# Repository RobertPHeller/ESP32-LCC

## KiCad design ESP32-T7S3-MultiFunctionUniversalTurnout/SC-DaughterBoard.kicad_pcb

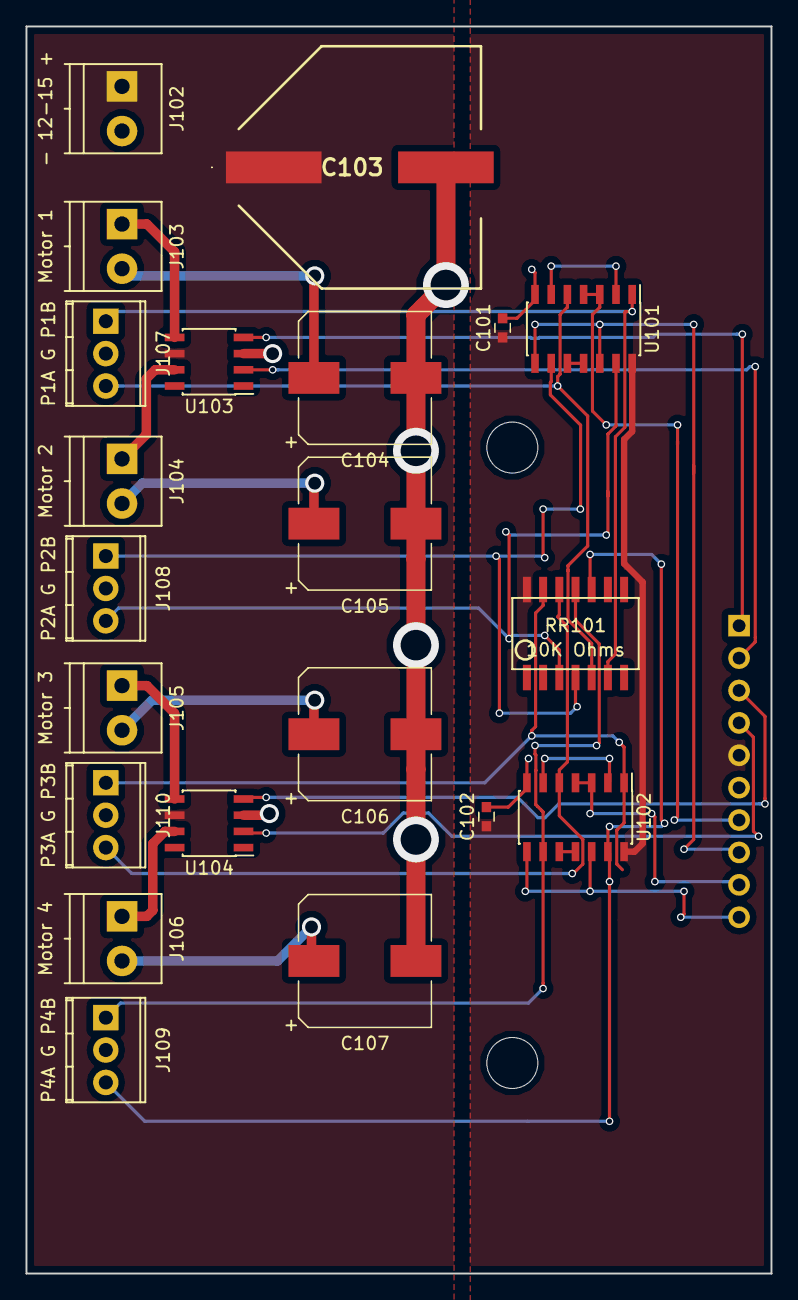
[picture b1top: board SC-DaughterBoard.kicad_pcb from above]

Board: 2 copper layers, 58.4 x 97.8 mm, 22 parts (1 on the bottom side), 31 nets.

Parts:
C101, C102: .1 uf; C_0603
C103: 4700uf 25V; EEEFK0J133SM
C104, C105, C106, C107: 1000uf 25V; CP_Elec_10x10.5
J101: IO_Port; Pin_Header_Straight_1x10_Pitch2.54mm
J102: - 12-15 +; TerminalBlock_Pheonix_PT-3.5mm_2pol
J103: Motor 1; TerminalBlock_Pheonix_PT-3.5mm_2pol
J104: Motor 2; TerminalBlock_Pheonix_PT-3.5mm_2pol
J105: Motor 3; TerminalBlock_Pheonix_PT-3.5mm_2pol
J106: Motor 4; TerminalBlock_Pheonix_PT-3.5mm_2pol
J107: P1A G P1B; TerminalBlock_Pheonix_MPT-2.54mm_3pol
J108: P2A G P2B; TerminalBlock_Pheonix_MPT-2.54mm_3pol
J109: P4A G P4B; TerminalBlock_Pheonix_MPT-2.54mm_3pol
J110: P3A G P3B; TerminalBlock_Pheonix_MPT-2.54mm_3pol
RR101: 10K Ohms; 4814P
U101, U102: 74HCT00; SOIC-14_3.9x8.7mm_Pitch1.27mm
U103, U104: TC4427; SOIC-8_3.9x4.9mm_Pitch1.27mm

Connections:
+3V3: C101.1, C102.1, J101.5, RR101.14, U101.14, U102.14
/Motor1: J101.1, U103.4
/Motor2: J101.2, U103.2
/Motor3: J101.3, U104.4
/Motor4: J101.4, U104.2
/P1A: J107.1, RR101.6, U101.1
/P1B: J107.3, RR101.5, U101.5
/P2A: J108.1, RR101.4, U101.9
/P2B: J108.3, RR101.3, U101.13
/P3A: J110.1, RR101.13, U102.1
/P3B: J110.3, RR101.12, U102.5
/P4A: J109.1, RR101.11, U102.9
/P4B: J109.3, RR101.10, U102.13
/Points1: J101.7, U101.3, U101.4
/Points2: J101.8, U101.8, U101.12
/Points3: J101.9, U102.3, U102.4
/Points4: J101.10, U102.8, U102.12
GND: C101.2, C102.2, C103.2, C104.2, C105.2, C106.2, C107.2, J101.6, J102.2, J107.2, J108.2, J109.2, J110.2, U101.7, U102.7, U103.3, U104.3
MotorPower: C103.1, J102.1, U103.6, U104.6
unnamed: C104.1, J103.2
unnamed: C105.1, J104.2
unnamed: C106.1, J105.2
unnamed: C107.1, J106.2
unnamed: J103.1, U103.5
unnamed: J104.1, U103.7
unnamed: J105.1, U104.5
unnamed: J106.1, U104.7
unnamed: U101.2, U101.6
unnamed: U101.10, U101.11
unnamed: U102.2, U102.6
unnamed: U102.10, U102.11

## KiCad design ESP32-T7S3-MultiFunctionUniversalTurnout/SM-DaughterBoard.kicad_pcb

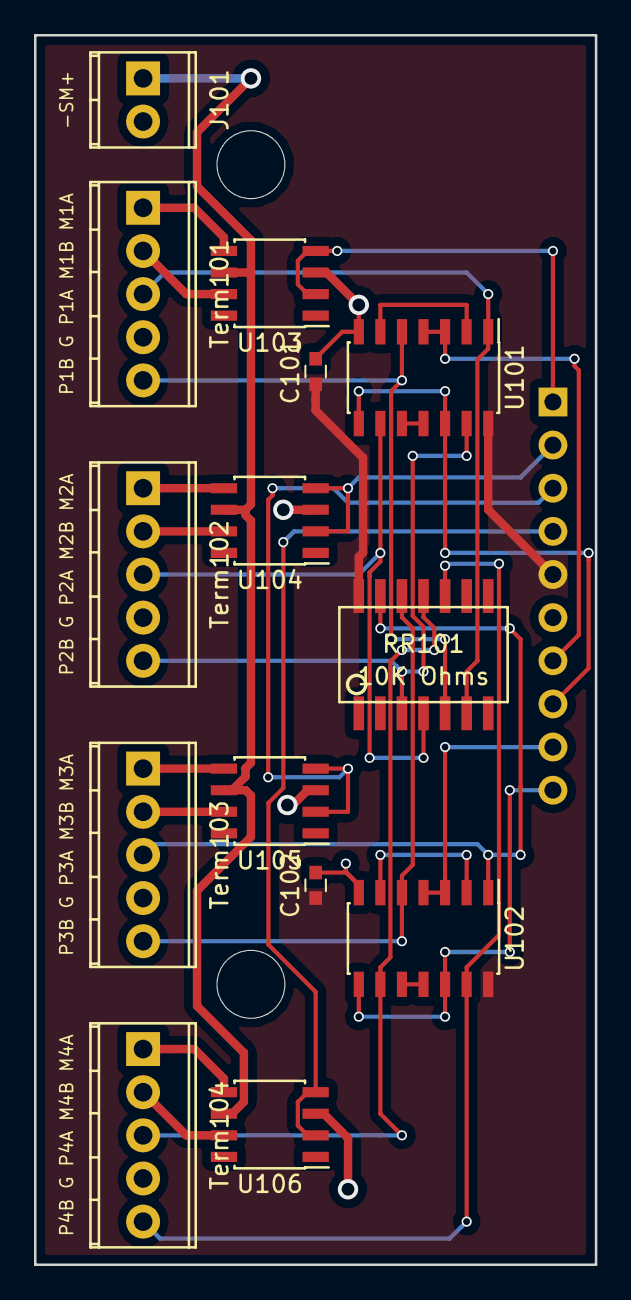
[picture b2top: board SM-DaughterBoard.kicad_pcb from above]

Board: 2 copper layers, 33.0 x 72.4 mm, 15 parts (1 on the bottom side), 31 nets.

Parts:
C101, C102: .1 uf; C_0603
J101: -SM+; TerminalBlock_Pheonix_MPT-2.54mm_2pol
J102: IO_Port; Pin_Header_Straight_1x10_Pitch2.54mm
RR101: 10K Ohms; 4814P
Term101: P1B G P1A M1B M1A; TerminalBlock_Pheonix_MPT-2.54mm_5pol
Term102: P2B G P2A M2B M2A; TerminalBlock_Pheonix_MPT-2.54mm_5pol
Term103: P3B G P3A M3B M3A; TerminalBlock_Pheonix_MPT-2.54mm_5pol
Term104: P4B G P4A M4B M4A; TerminalBlock_Pheonix_MPT-2.54mm_5pol
U101, U102: 74HCT00; SOIC-14_3.9x8.7mm_Pitch1.27mm
U103, U104, U105, U106: TC4428; SOIC-8_3.9x4.9mm_Pitch1.27mm

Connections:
+3V3: C101.1, C102.1, J102.5, RR101.14, U101.14, U102.14
/M1A: Term101.1, U103.5
/M1B: Term101.2, U103.7
/M2A: Term102.1, U104.5
/M2B: Term102.2, U104.7
/M3A: Term103.1, U105.5
/M3B: Term103.2, U105.7
/M4A: Term104.1, U106.5
/M4B: Term104.2, U106.7
/Motor1: J102.1, U103.2, U103.4
/Motor2: J102.2, U104.2, U104.4
/Motor3: J102.3, U105.2, U105.4
/Motor4: J102.4, U106.2, U106.4
/P1A: RR101.6, Term101.3, U101.1
/P1B: RR101.5, Term101.5, U101.5
/P2A: RR101.4, Term102.3, U101.9
/P2B: RR101.3, Term102.5, U101.13
/P3A: RR101.13, Term103.3, U102.1
/P3B: RR101.12, Term103.5, U102.5
/P4A: RR101.11, Term104.3, U102.9
/P4B: RR101.10, Term104.5, U102.13
/Points1: J102.7, U101.3, U101.4
/Points2: J102.8, U101.8, U101.12
/Points3: J102.9, U102.3, U102.4
/Points4: J102.10, U102.8, U102.12
GND: C101.2, C102.2, J101.2, J102.6, Term101.4, Term102.4, Term103.4, Term104.4, U101.7, U102.7, U103.3, U104.3, U105.3, U106.3
unnamed: U101.2, U101.6
unnamed: U101.10, U101.11
unnamed: U102.2, U102.6
unnamed: U102.10, U102.11
SMPower: J101.1, U103.6, U104.6, U105.6, U106.6

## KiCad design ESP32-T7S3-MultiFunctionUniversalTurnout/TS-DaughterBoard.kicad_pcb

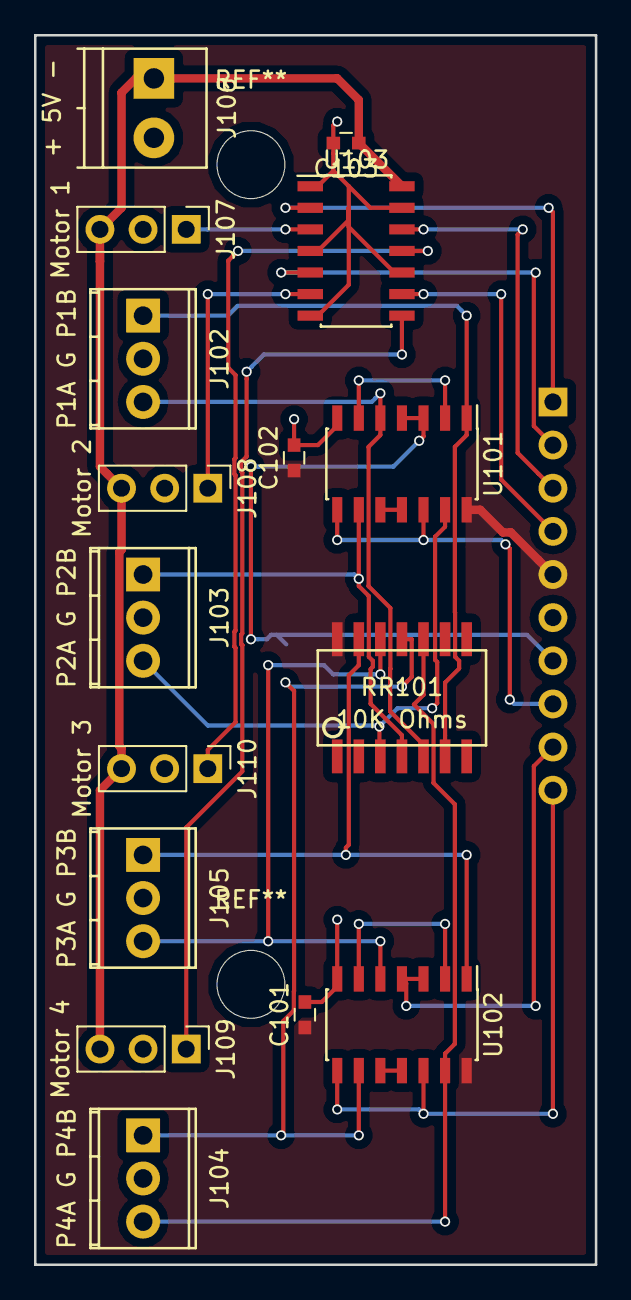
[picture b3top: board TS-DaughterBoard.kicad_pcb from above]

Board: 2 copper layers, 33.0 x 72.4 mm, 17 parts (1 on the bottom side), 27 nets.

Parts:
C101, C102: .1 uf; C_0603
C103: .1uf; C_0603
J101: IO_Port; Pin_Header_Straight_1x10_Pitch2.54mm
J102: P1A G P1B; TerminalBlock_Pheonix_MPT-2.54mm_3pol
J103: P2A G P2B; TerminalBlock_Pheonix_MPT-2.54mm_3pol
J104: P4A G P4B; TerminalBlock_Pheonix_MPT-2.54mm_3pol
J105: P3A G P3B; TerminalBlock_Pheonix_MPT-2.54mm_3pol
J106: + 5V -; TerminalBlock_Pheonix_PT-3.5mm_2pol
J107: Motor 1; Pin_Header_Straight_1x03_Pitch2.54mm
J108: Motor 2; Pin_Header_Straight_1x03_Pitch2.54mm
J109: Motor 4; Pin_Header_Straight_1x03_Pitch2.54mm
J110: Motor 3; Pin_Header_Straight_1x03_Pitch2.54mm
RR101: 10K Ohms; 4814P
U101, U102: 74HCT00; SOIC-14_3.9x8.7mm_Pitch1.27mm
U103: 74LV125AN; SOIC-14_3.9x8.7mm_Pitch1.27mm

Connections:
+3V3: C101.1, C102.1, J101.5, RR101.14, U101.14, U102.14
+5V: C103.1, J106.1, J107.3, J108.3, J109.3, J110.3, U103.14
/Motor1: J101.1, U103.2
/Motor2: J101.2, U103.5
/Motor3: J101.3, U103.12
/Motor4: J101.4, U103.9
/P1A: J102.1, RR101.6, U101.1
/P1B: J102.3, RR101.5, U101.5
/P2A: J103.1, RR101.4, U101.9
/P2B: J103.3, RR101.3, U101.13
/P3A: J105.1, RR101.13, U102.1
/P3B: J105.3, RR101.12, U102.5
/P4A: J104.1, RR101.11, U102.9
/P4B: J104.3, RR101.10, U102.13
/Points1: J101.7, U101.3, U101.4
/Points2: J101.8, U101.8, U101.12
/Points3: J101.9, U102.3, U102.4
/Points4: J101.10, U102.8, U102.12
GND: C101.2, C102.2, C103.2, J101.6, J102.2, J103.2, J104.2, J105.2, J106.2, J107.2, J108.2, J109.2, J110.2, U101.7, U102.7, U103.1, U103.4, U103.7, U103.10, U103.13
unnamed: J107.1, U103.3
unnamed: J108.1, U103.6
unnamed: J109.1, U103.8
unnamed: J110.1, U103.11
unnamed: U101.2, U101.6
unnamed: U101.10, U101.11
unnamed: U102.2, U102.6
unnamed: U102.10, U102.11

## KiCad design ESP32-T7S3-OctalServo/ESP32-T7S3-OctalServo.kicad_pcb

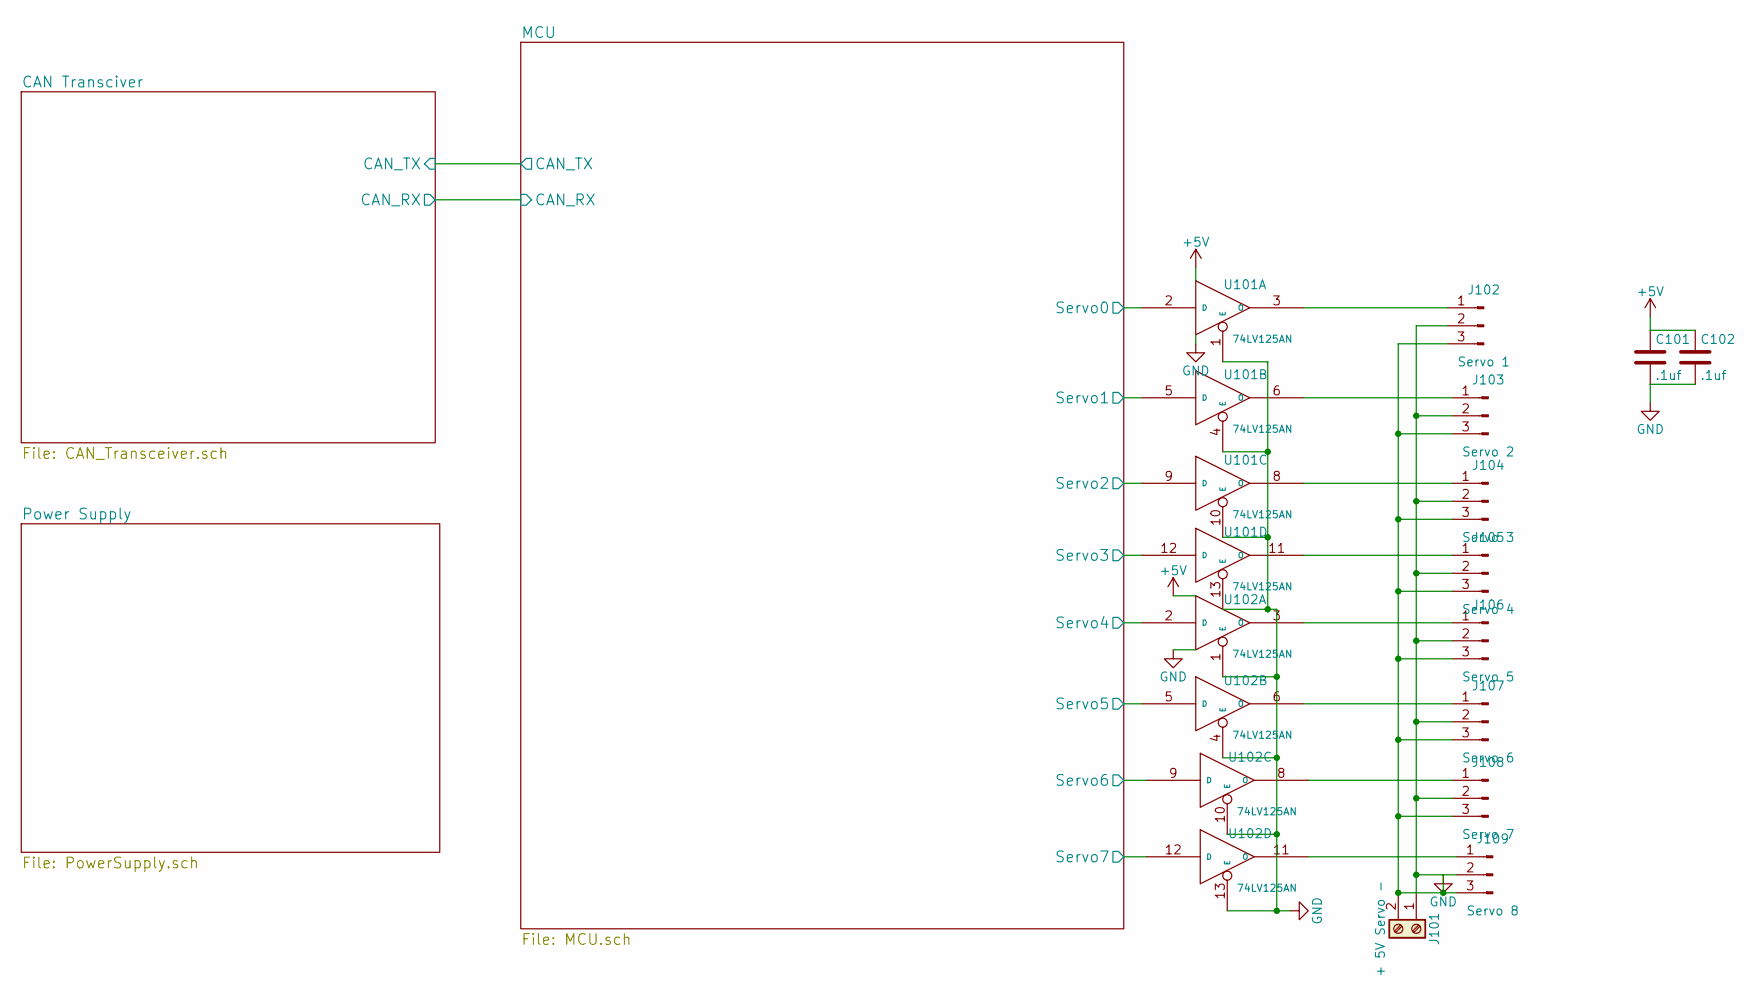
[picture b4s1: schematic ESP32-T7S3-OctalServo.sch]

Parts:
C101, C102: .1uf; C_0603
J101: + 5V Servo -; TerminalBlock_Pheonix_PT-3.5mm_2pol
J102: Servo 1; Pin_Header_Straight_1x03_Pitch2.54mm
J103: Servo 2; Pin_Header_Straight_1x03_Pitch2.54mm
J104: Servo 3; Pin_Header_Straight_1x03_Pitch2.54mm
J105: Servo 4; Pin_Header_Straight_1x03_Pitch2.54mm
J106: Servo 5; Pin_Header_Straight_1x03_Pitch2.54mm
J107: Servo 6; Pin_Header_Straight_1x03_Pitch2.54mm
J108: Servo 7; Pin_Header_Straight_1x03_Pitch2.54mm
J109: Servo 8; Pin_Header_Straight_1x03_Pitch2.54mm
U101, U102: 74LV125AN; SOIC-14_3.9x8.7mm_Pitch1.27mm; Mouser Part Number 771-AHCT125D118

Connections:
+5V: C101.1, C102.1, U101.14 (VCC), U102.14 (VCC); also elsewhere on the board
/MCU/Servo0: U101.2 (D); also elsewhere on the board
/MCU/Servo1: U101.5 (D); also elsewhere on the board
/MCU/Servo2: U101.9 (D); also elsewhere on the board
/MCU/Servo3: U101.12 (D); also elsewhere on the board
/MCU/Servo4: U102.2 (D); also elsewhere on the board
/MCU/Servo5: U102.5 (D); also elsewhere on the board
/MCU/Servo6: U102.9 (D); also elsewhere on the board
/MCU/Servo7: U102.12 (D); also elsewhere on the board
unnamed: J102.1, U101.3 (O)
unnamed: J103.1, U101.6 (O)
unnamed: J104.1, U101.8 (O)
unnamed: J105.1, U101.11 (O)
unnamed: J106.1, U102.3 (O)
unnamed: J107.1, U102.6 (O)
unnamed: J108.1, U102.8 (O)
unnamed: J109.1, U102.11 (O)

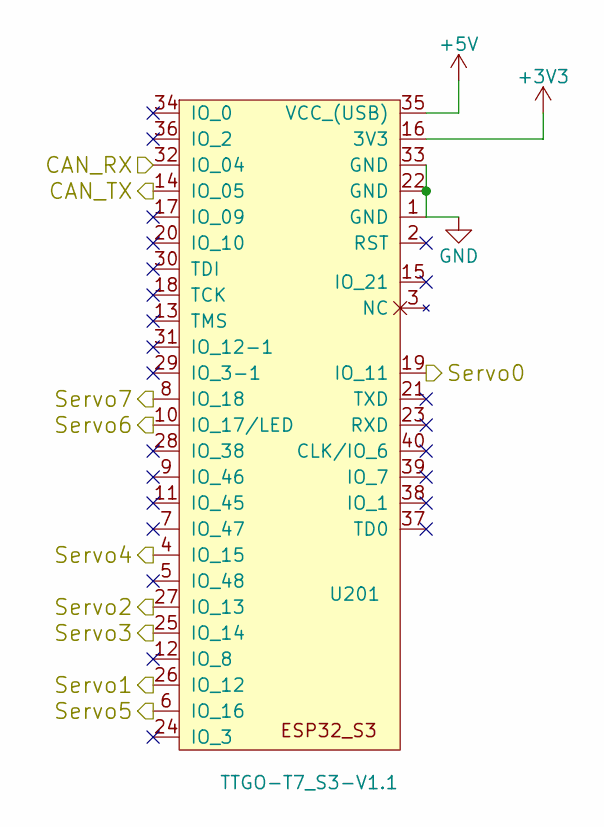
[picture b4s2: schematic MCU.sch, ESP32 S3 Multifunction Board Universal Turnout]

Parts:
U201: TTGO-T7_S3-V1.1; ESP32_mini

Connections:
+3V3: U201.16 (3V3); also elsewhere on the board
+5V: U201.35 (VCC_(USB)); also elsewhere on the board
/CAN Transciver/CAN_RX: U201.32 (IO_04); also elsewhere on the board
/CAN Transciver/CAN_TX: U201.14 (IO_05); also elsewhere on the board
/MCU/Servo0: U201.19 (IO_11); also elsewhere on the board
/MCU/Servo1: U201.26 (IO_12); also elsewhere on the board
/MCU/Servo2: U201.27 (IO_13); also elsewhere on the board
/MCU/Servo3: U201.25 (IO_14); also elsewhere on the board
/MCU/Servo4: U201.4 (IO_15); also elsewhere on the board
/MCU/Servo5: U201.6 (IO_16); also elsewhere on the board
/MCU/Servo6: U201.10 (IO_17/LED); also elsewhere on the board
/MCU/Servo7: U201.8 (IO_18); also elsewhere on the board

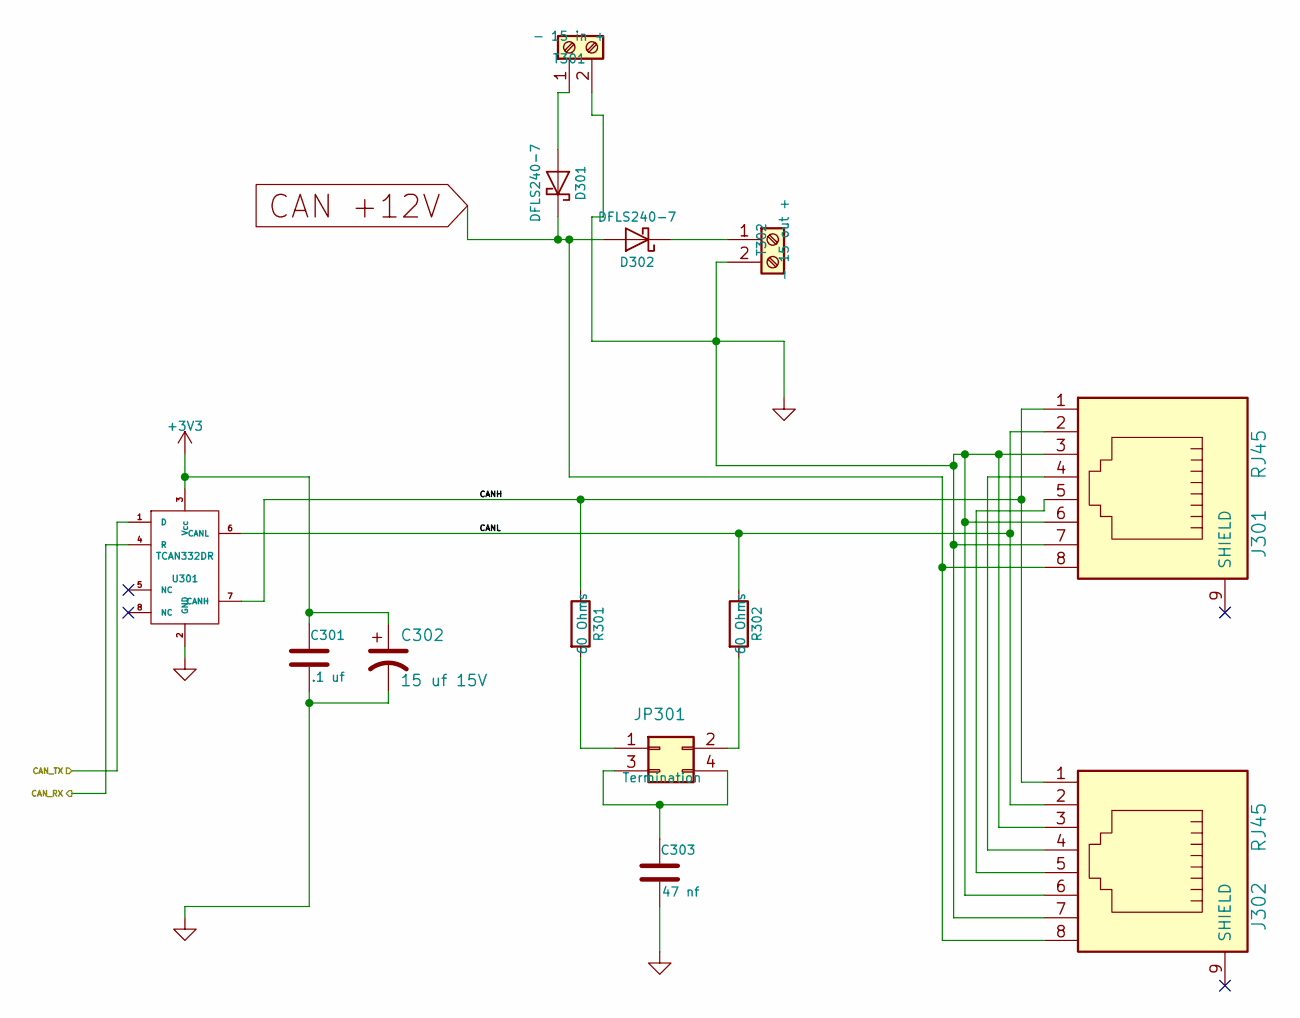
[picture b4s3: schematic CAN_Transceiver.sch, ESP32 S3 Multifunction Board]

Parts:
C301: .1 uf; C_0603; Mouser Part Number 710-885012206095
C302: 15 uf 15V; CP_Elec_4x5.7; Mouser Part Number 647-UUD1C150MCL
C303: 47 nf; C_0603; Mouser Part Number 710-885012206093
D301, D302: DFLS240-7; D_PowerDI-123; Mouser Part Number 621-DFLS240-7
J301, J302: RJ45; RJ45_8; Mouser Part Number 710-615008144221
JP301: Termination; Pin_Header_Straight_2x02_Pitch2.54mm; Mouser Part Number 649-67997-404HLF
R301, R302: 60 Ohms; R_1206; Mouser Part Number 71-CRCW120660R0KNAIF
T301: - 15 in +; TerminalBlock_Pheonix_MPT-2.54mm_2pol; Mouser Part Number 651-1725656
T302: - 15 out +; TerminalBlock_Pheonix_MPT-2.54mm_2pol; Mouser Part Number 651-1725656
U301: TCAN332DR; SOIC-8_3.9x4.9mm_Pitch1.27mm; Mouser Part Number 595-TCAN332DR

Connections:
+3V3: C301.1, C302.1, U301.3 (Vcc); also elsewhere on the board
/CAN Transciver/CANH: J301.1, J302.1, R301.1, U301.7 (CANH)
/CAN Transciver/CANL: J301.2, J302.2, R302.1, U301.6 (CANL)
/CAN Transciver/CAN_RX: U301.4 (R); also elsewhere on the board
/CAN Transciver/CAN_TX: U301.1 (D); also elsewhere on the board
CAN +12V: D301.1 (K), D302.2 (A), J301.8, J302.8; also elsewhere on the board
unnamed: C303.1, JP301.3, JP301.4
unnamed: D301.2 (A), T301.1
unnamed: D302.1 (K), T302.1
unnamed: J301.4, J302.4
unnamed: J301.5, J302.5
unnamed: JP301.1, R301.2
unnamed: JP301.2, R302.2

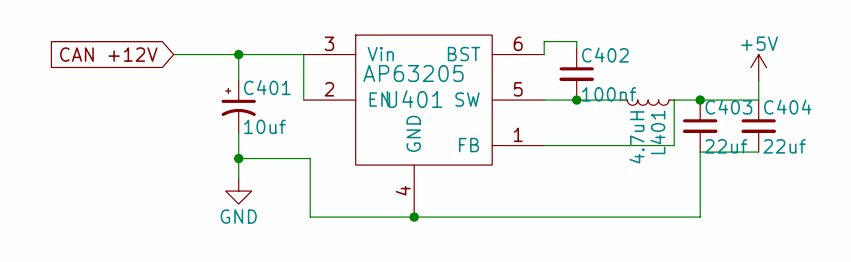
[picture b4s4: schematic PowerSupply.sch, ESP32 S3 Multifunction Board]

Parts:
C401: 10uf; CP_Elec_5x5.3; Mouser Part Number 710-865230542002
C402: 100nf; C_0603; Mouser Part Number 710-885012206020
C403, C404: 22uf; C_0603; Mouser Part Number 603-CC0603MRX6S5B226
L401: 4.7uH; L_7.3x7.3_H4.5; Mouser Part Number 81-B1047AS-4R7NP3
U401: AP63205; TSOT-23-6_MK06A; Mouser Part Number 621-AP63205WU-7

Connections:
+5V: C403.1, C404.1, L401.1, U401.1 (FB); also elsewhere on the board
CAN +12V: C401.1, U401.2 (EN), U401.3 (Vin); also elsewhere on the board
unnamed: C402.1, U401.6 (BST)
unnamed: C402.2, L401.2, U401.5 (SW)

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
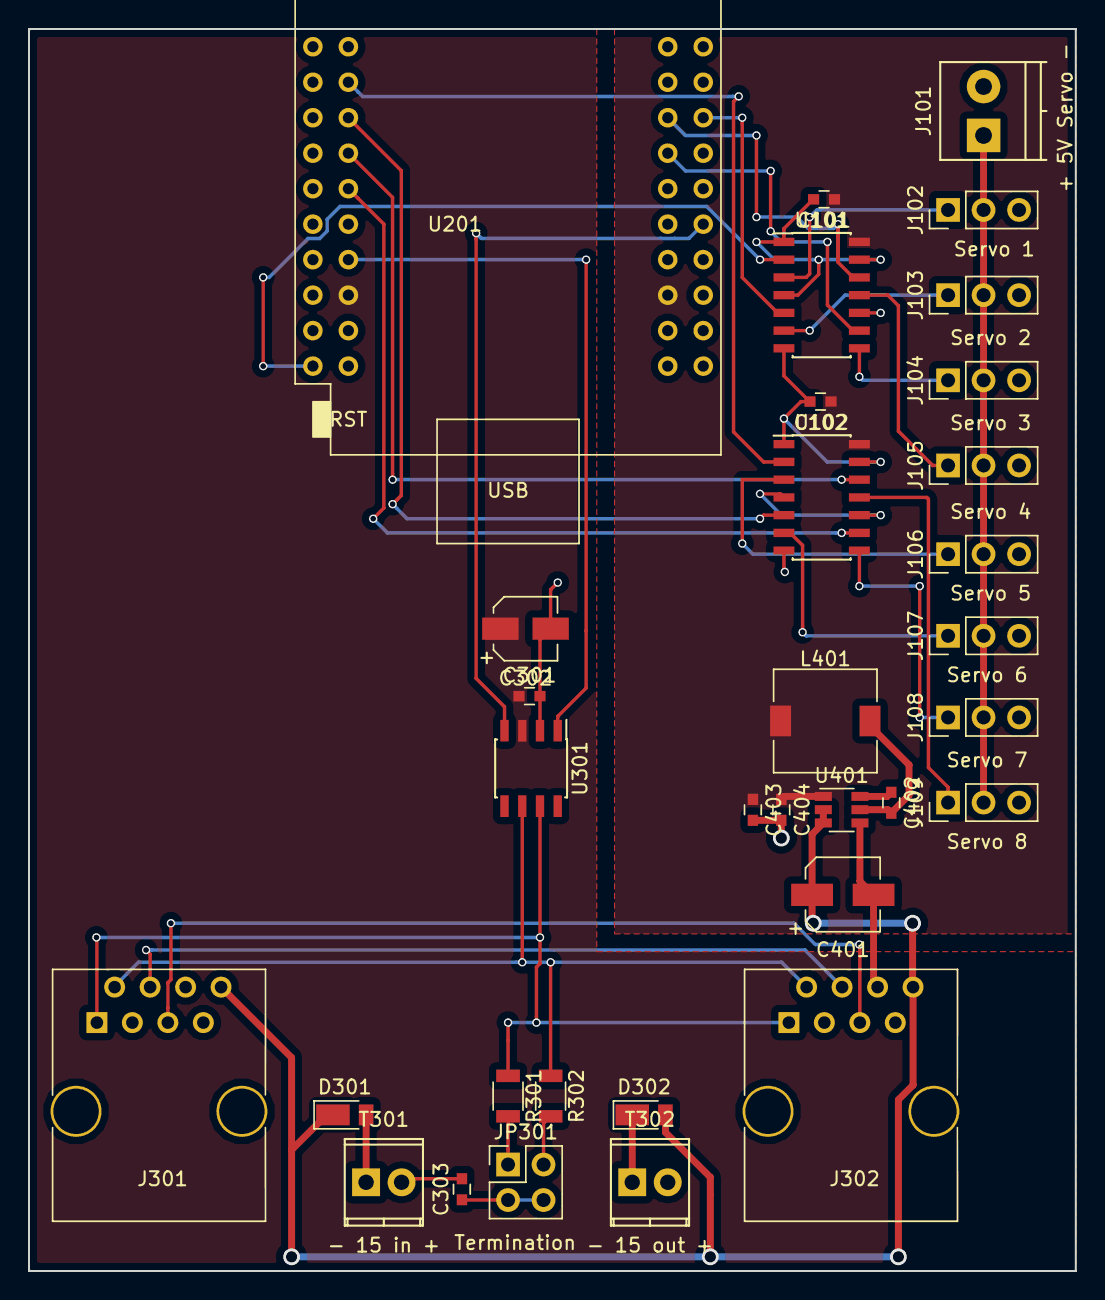
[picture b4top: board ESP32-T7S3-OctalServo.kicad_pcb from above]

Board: 2 copper layers, 74.9 x 88.9 mm, 33 parts (0 on the bottom side), 34 nets.
